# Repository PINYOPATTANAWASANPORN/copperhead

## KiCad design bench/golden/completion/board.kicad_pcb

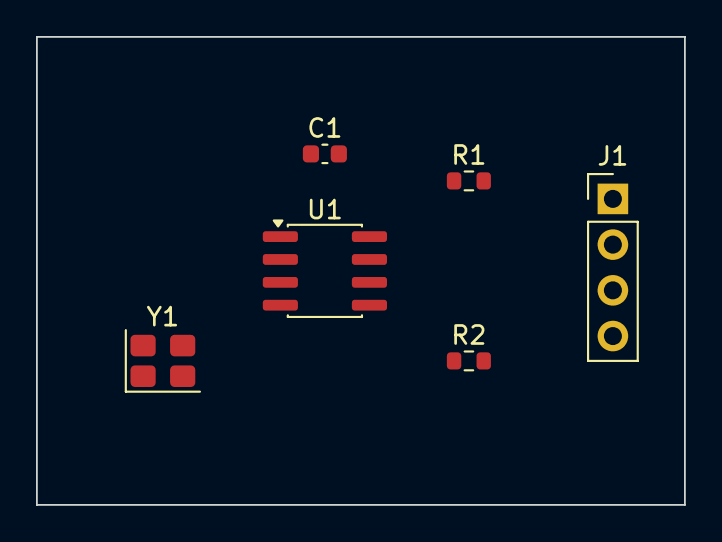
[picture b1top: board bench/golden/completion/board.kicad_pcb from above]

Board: 2 copper layers, 36.0 x 26.0 mm, 6 parts (0 on the bottom side), 6 nets, no tracks yet.

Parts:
C1: 100n; C_0603_1608Metric
J1: CONN; PinHeader_1x04_P2.54mm_Vertical
R1, R2: 10k; R_0603_1608Metric
U1: MCU; SOIC-8_3.9x4.9mm_P1.27mm
Y1: 8MHz; Crystal_SMD_3225-4Pin_3.2x2.5mm

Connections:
GND: C1.2, J1.2, U1.4, Y1.2, Y1.4
SIG1: J1.3, R1.2, U1.1
SIG2: J1.4, R2.2, U1.2
VCC: C1.1, J1.1, R1.1, R2.1, U1.8
XI: U1.5, Y1.1
XO: U1.6, Y1.3

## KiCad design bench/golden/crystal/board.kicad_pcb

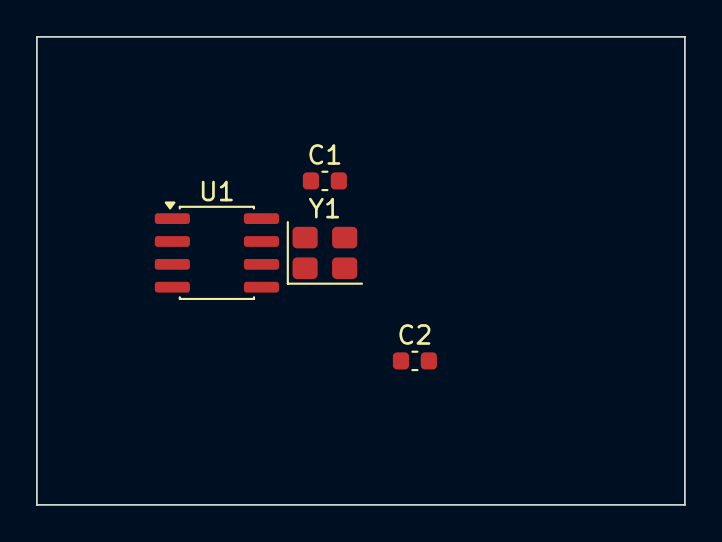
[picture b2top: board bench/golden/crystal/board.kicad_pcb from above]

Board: 2 copper layers, 36.0 x 26.0 mm, 4 parts (0 on the bottom side), 3 nets, no tracks yet.

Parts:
C1, C2: 22p; C_0603_1608Metric
U1: MCU; SOIC-8_3.9x4.9mm_P1.27mm
Y1: 16M; Crystal_SMD_3225-4Pin_3.2x2.5mm

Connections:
GND: C1.2, C2.2, U1.4, Y1.2, Y1.4
XI: C1.1, U1.1, Y1.1
XO: C2.1, U1.2, Y1.3

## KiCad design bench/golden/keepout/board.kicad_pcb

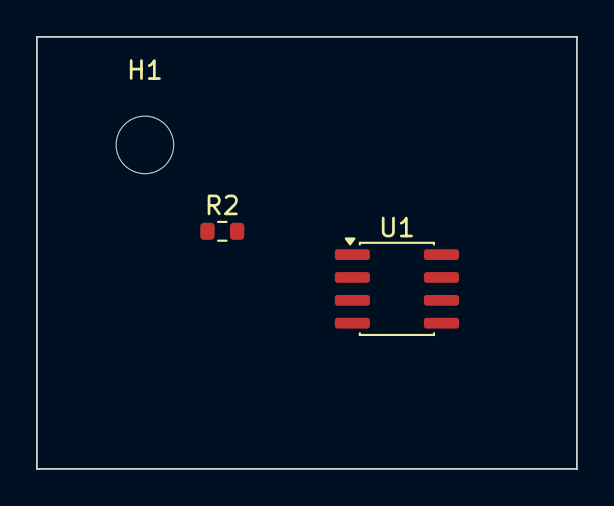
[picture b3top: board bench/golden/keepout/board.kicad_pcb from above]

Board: 2 copper layers, 30.0 x 24.0 mm, 3 parts (0 on the bottom side), 2 nets, no tracks yet.

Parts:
H1: M3; MountingHole_3.2mm_M3
R2: 4k7; R_0603_1608Metric
U1: MCU; SOIC-8_3.9x4.9mm_P1.27mm

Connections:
SIG: R2.1, U1.2
VCC: R2.2, U1.8

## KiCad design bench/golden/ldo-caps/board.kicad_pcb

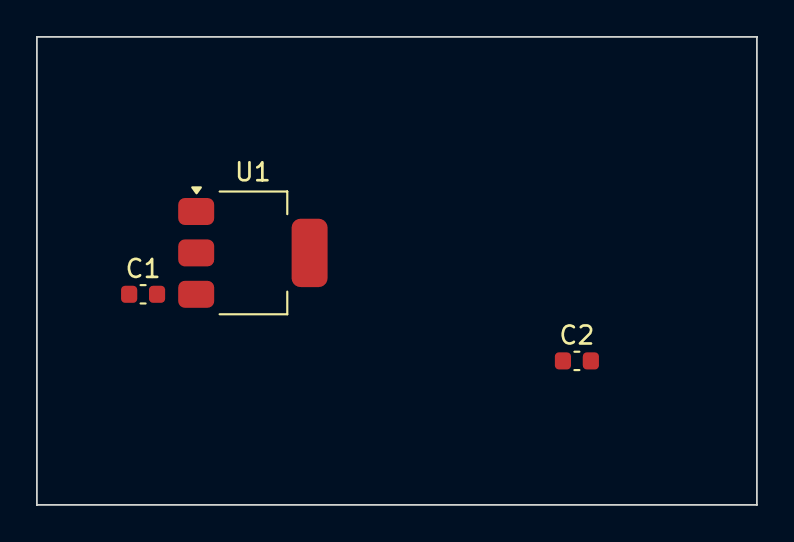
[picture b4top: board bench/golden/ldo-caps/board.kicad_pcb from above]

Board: 2 copper layers, 40.0 x 26.0 mm, 3 parts (0 on the bottom side), 3 nets, no tracks yet.

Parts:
C1, C2: 10u; C_0603_1608Metric
U1: AMS1117-3.3; SOT-223-3_TabPin2

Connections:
GND: C1.2, C2.2, U1.1
VIN: C1.1, U1.3
VOUT: C2.1, U1.2

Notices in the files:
bench/golden/completion/board.kicad_pcb:
copperhead golden microboard; footprints from the KiCad libraries (CC-BY-SA-4.0 with the KiCad library exception)
